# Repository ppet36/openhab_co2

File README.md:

# OpenHAB CO2 sensor

This repository contains Cadsoft's Eagle schematic and PCBs as well as Arduino firmware for CO2 monitoring device based on ESP8266-01 and relatively cheap CO2 sensor MH-Z19. Device is designed to be powered from USB charger.

## Schematic & PCB

On schematic is nothing special. Two available pins of ESP01 module is used for serial communication with sensor at 9600 baud rate.

Board is designed as single-sided with some wire jumpers.

## Firmware

Firmware can be programmed via Arduino IDE. After device startup MH-Z19 sensor returns different values before it is heated up. Firmware first waits for sequence of 400PPM readings and after that for value different than 400PPM; then is sensor heated up and ready for measuring.

WIFI access point and network parameters can be set in source code. After device startup and sensor heated up is on his IP address available HTTP server, which provides measured CO2 PPM value as REST service. Via HTTP server is also available simple configuration page where some parameters can be changed.

Sensor is very sensitive so firmware averages 50 values (by default) for eliminate jitter. Number of averaged values, frequency of reading values from sensor and other parameters can be set in source file or via WEB configuration page. Configuration page is written in very primitive HTML so can be accessed for example from terminal browser; for example "links":

```
links http://192.168.128.209/
```

## OpenHAB

Configuration in OpenHAB is very simple. First you need to define item (in your *.items file) with correct IP address of device.
```
Number co2PPM "Indoor CO2 [%s PPM]" <co2> { http="<[http://192.168.128.209/co2:15000:JS(intvalue.js)]" } 
```
After item definition is ready, OpenHAB reads every 15 seconds CO2 value from device. To display measured value you need modify your sitemap file. It's also very easy.
```
Text item=co2PPM
```
After successfull definition OpenHAB GUI shows simple text item:

## Case
In openscad directory can be found simple case for whole device. There is OpenSCAD source file as well as rendered STL model.

## Some images

Print is not perfect because my printer bed is too dirty. But this is not problem; device will be on cabinet.

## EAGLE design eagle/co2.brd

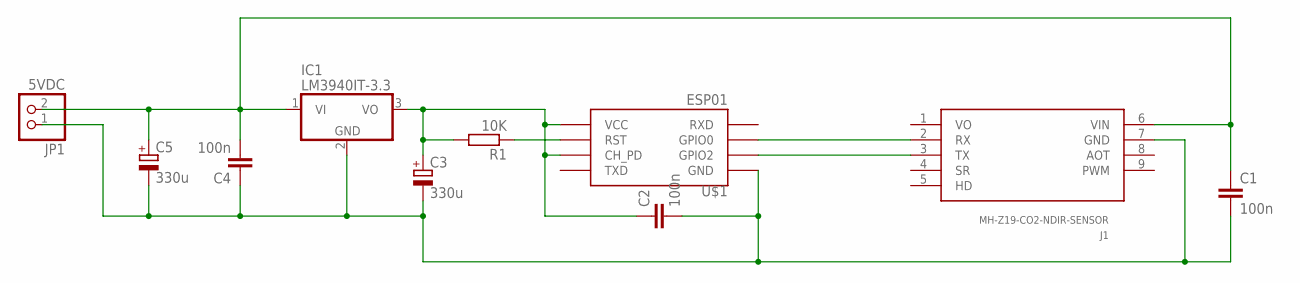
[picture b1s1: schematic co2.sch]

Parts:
C1, C2, C4: 100n; C050-025X075
C3, C5: 330u; E2,5-6
IC1: LM3940IT-3.3; TO220H
J1: MH-Z19-CO2-NDIR-SENSOR; MH-Z19
JP1: 5VDC; 1X02
R1: 10K; 0204/7
U$1: ESP01

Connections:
+3.3V: C2.1, C3.+, IC1.3 (VO), R1.2, U$1.CH_PD, U$1.VCC
+5V: C1.1, C4.2, C5.+, IC1.1 (VI), J1.6 (VIN), JP1.2
GND: C1.2, C2.2, C3.-, C4.1, C5.-, IC1.2 (GND), J1.7 (GND), JP1.1, U$1.GND
unnamed: J1.2 (RX), U$1.GPIO0
unnamed: J1.3 (TX), U$1.GPIO2
unnamed: R1.1, U$1.RST
VO: J1.1 (VO)

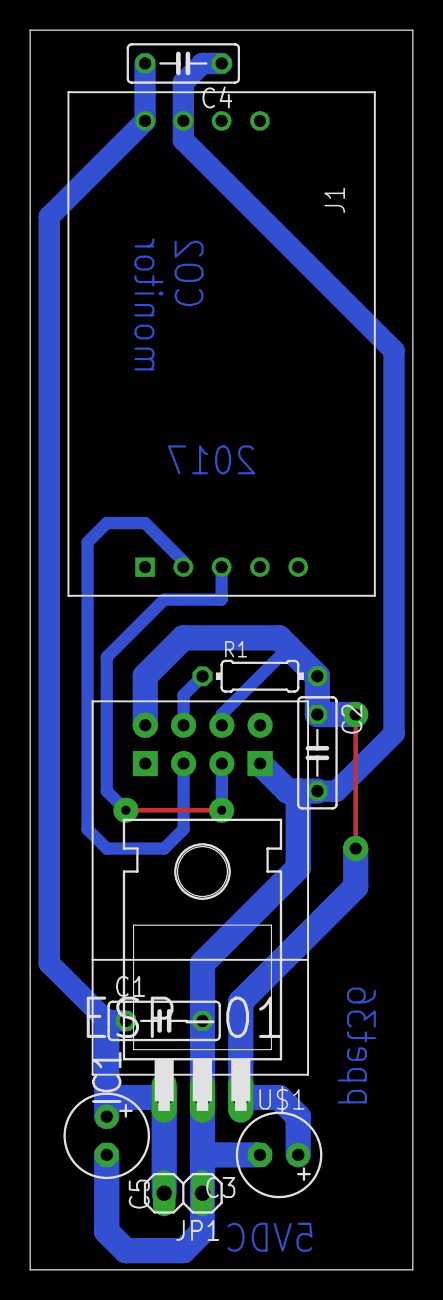
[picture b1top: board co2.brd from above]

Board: 2 copper layers, 25.4 x 82.2 mm, 10 parts (0 on the bottom side), 6 nets.
